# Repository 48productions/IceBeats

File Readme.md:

# IceBeats Music Visualizer
*"it's like a firebeat, but **cooler**"*

## Introduction
IceBeats is a Teensy-based lights driver board that does two things:
 - Works with StepMania to control cabinet and pad lights in a 573-era DDR cabinet.
 - Real-time, hardware independent music visualization across two LED strips.

The hardware is designed for minimal components/configuration for an embedded environment.
Grab a Teensy 3.2, a few addressable LED strips, and a few basic components, and you're done! No bloated bluetooth/wifi control or complex hardware setup required.

## Features
Code support for these are built-in - all 99% configurable, use any combination you like!

 * Visualization addressable LED strip - An addressable RGB LED strip for visualizations.
 * Bass addressable LED strip - Another addressable RGB LED strip, blinks to the beat.
 * Bass single-color LED strip/strand - Designed for a single-color LED strip, or low voltage LED string lights. Blinks to the beat.
     * Supports two-wire LED strands, where alternate LEDs/colors are driven by reversing the strip polarity using a H-Bridge, like the L293D. These are cheap and readibly available off places like Amazon.

 * Accepts audio input via RCA/mono 3.5mm jack (or with modification, any other input the Teensy audio library supports)
 * Designed around Teensy 3.2, other Audio-capable Teensy boards likely compatible (the 4.0 is untested but may work)
 
 * FFT-based music visualization using the Teensy Audio Library
 * Multiple visualization effects and color palettes. Optional dynamic, music-based color palettes available
 * Idle animations for when no music is playing
 
 * Drives 573-era DanceDanceRevolution cabinet/pad lighting (reads SextetStream-formatted data output by StepMania or other programs).
 * PCB design

## Hardware Setup
**Pin numbers and LED strip lengths can ALL be configured in `IceBeats.ino` - the settings are at the top!**

### Audio Input
Audio input is taken via a 3.5mm/RCA jack. [Wiring instructions can be found on the Teensy Audio Design Tool](https://www.pjrc.com/teensy/gui/?info=AudioInputAnalog)'s info panel for AudioInputAnalog.

### Visualization LED strip:
The main attraction, music visualization on an addressable LED strip!

Any WS2812/NeoPixel strip will do here (default: 54 pixels long, but can be configured for shorter/longer strips).
Excessive pixel count may cause performance drops.

### Bass LED strip:
This blinks to the beat with a strip-wide gradient, occasionally changing colors.

Again, use any WS2812/NeoPixel strip (default: 128 pixels. This can be made shorter/longer too)

### Bass light strand:
This one just blinks to the beat! You've got a few options for this:

For a single-color LED strip/string, one PWM pin is used for setting the strip's brightness, just hook it up to a mosfet/transistor and you're good to go.
  
Some cheap LED strings on Amazon will control alternate LEDs, or different LED colors by reversing the strip polarity.
If you have one of these strings, a L293D can be used to drive the strip at two different polarities to turn on alternate LEDs/colors.
Another pin can optionally connect to a L293D to do this. You will need to invert that pin's signal via a transistor, inverter, etc to drive the second input on the L293D.

### StepMania pad/cab light control:
This code accepts input over serial for any games/tools that use the SextetStream protocol for driving DDR cabinet/pad lights.

In the case of StepMania, this means either using the SextetStreamToFile (Linux) or Win32Serial (Windows) lights driver.

The light states are sent to the rest of the Teensy's IO pins. Ideally, these should connect to the DDR cabinet through opto isolators. No transistor/mosfet is needed here, the stock DDR cabinet amp handles the high-current loads.

Lights data can optionally be output to three shift registers, as well, if you need more light outputs than the Teensy has pins.

## Todo:
 There's a lotta things that could be improved
 * Better documentation/wiring instructions
 * A few bugfixes with idle animations on the main led strip
 * Better beat detection
 * Getting the visualizations to look like they reflect the music a bit closer
 * More color palettes.

## License
I'd greatly apprecate it if you credit/link back to this repo if you use this code somewhere - this thing took a TON of time to make.

That being said,

¯\\_(ツ)_/¯

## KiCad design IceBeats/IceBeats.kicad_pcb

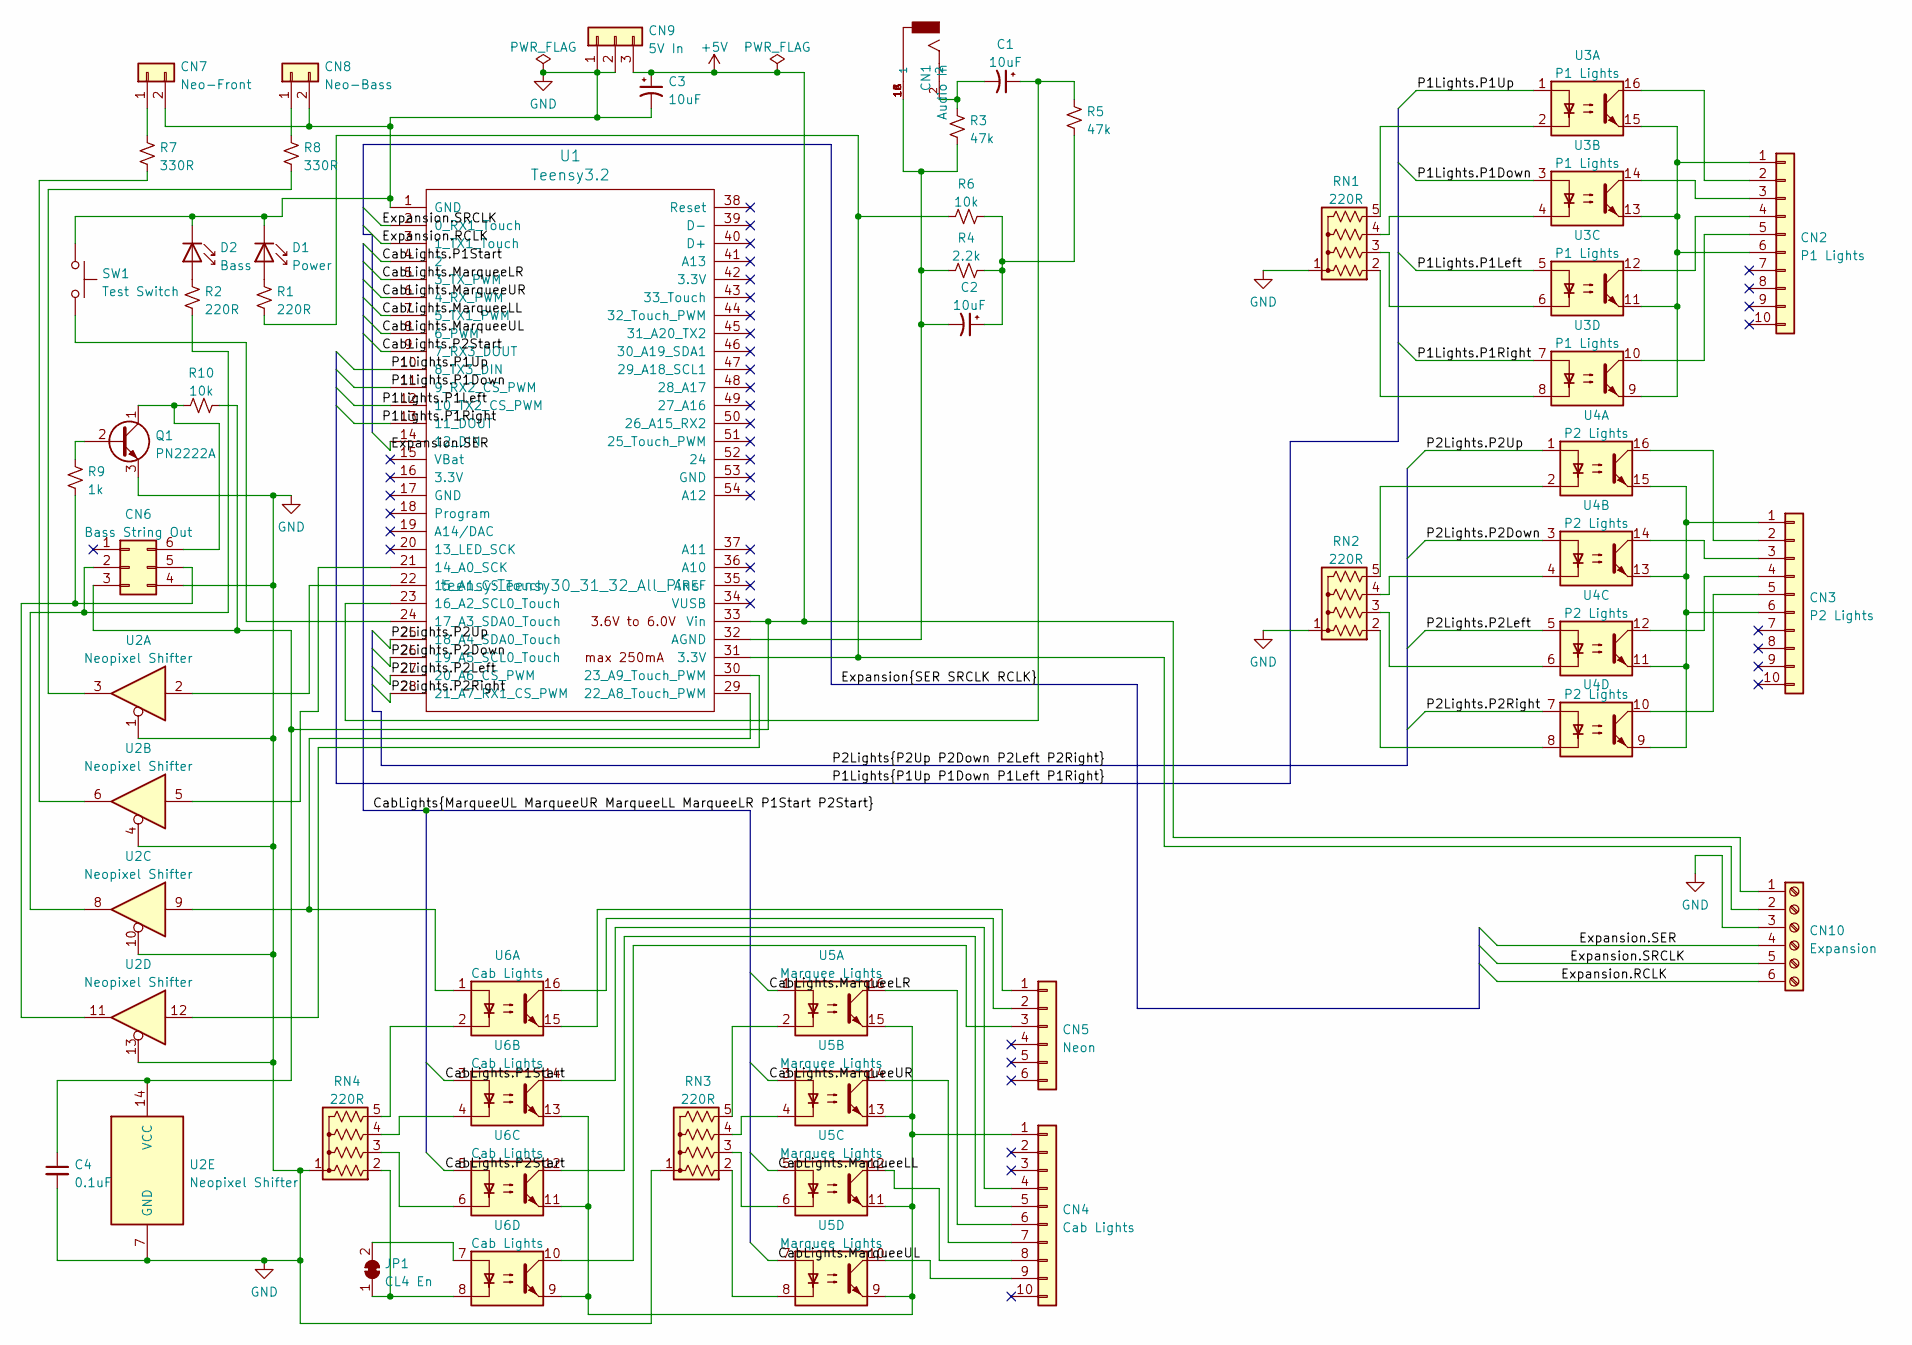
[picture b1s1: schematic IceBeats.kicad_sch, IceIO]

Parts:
C1, C2, C3: 10uF; CP_Radial_D6.3mm_P2.50mm
C4: 0.1uF; C_Disc_D5.1mm_W3.2mm_P5.00mm
CN1: Audio In; CUI_RCJ-013; PART_REV B
CN2: P1 Lights; PinHeader_1x10_P2.54mm_Vertical
CN3: P2 Lights; PinHeader_1x10_P2.54mm_Vertical
CN4: Cab Lights; PinHeader_1x10_P2.54mm_Vertical
CN5: Neon; PinHeader_1x06_P2.54mm_Vertical
CN6: Bass String Out; IDC-Header_2x03_P2.54mm_Vertical
CN7: Neo-Front; Molex_KK-254_AE-6410-02A_1x02_P2.54mm_Vertical
CN8: Neo-Bass; Molex_KK-254_AE-6410-02A_1x02_P2.54mm_Vertical
CN9: 5V In; Molex_KK-254_AE-6410-03A_1x03_P2.54mm_Vertical
CN10: Expansion; PinHeader_1x06_P2.54mm_Vertical
D1: Power; LED_D3.0mm_Horizontal_O3.81mm_Z2.0mm
D2: Bass; LED_D3.0mm_Horizontal_O3.81mm_Z2.0mm
JP1: CL4 En; SolderJumper-2_P1.3mm_Bridged_RoundedPad1.0x1.5mm
Q1: PN2222A; TO-92_HandSolder
R1, R2: 220R; R_Axial_DIN0207_L6.3mm_D2.5mm_P2.54mm_Vertical
R3: 47k; R_Axial_DIN0207_L6.3mm_D2.5mm_P2.54mm_Vertical
R4: 2.2k; R_Axial_DIN0207_L6.3mm_D2.5mm_P10.16mm_Horizontal
R5: 47k; R_Axial_DIN0207_L6.3mm_D2.5mm_P10.16mm_Horizontal
R6, R10: 10k; R_Axial_DIN0207_L6.3mm_D2.5mm_P10.16mm_Horizontal
R7, R8: 330R; R_Axial_DIN0207_L6.3mm_D2.5mm_P10.16mm_Horizontal
R9: 1k; R_Axial_DIN0207_L6.3mm_D2.5mm_P10.16mm_Horizontal
RN1, RN2, RN3, RN4: 220R; R_Array_SIP5
SW1: Test Switch; SW_PUSH_6mm_H5mm
U1: Teensy3.2; Teensy30_31_32_All_Pins
U2: Neopixel Shifter; DIP-14_W7.62mm_Socket
U3: P1 Lights; DIP-16_W7.62mm
U4: P2 Lights; DIP-16_W7.62mm
U5: Marquee Lights; DIP-16_W7.62mm
U6: Cab Lights; DIP-16_W7.62mm

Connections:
+5V: C3.1, C4.1, CN6.3, CN9.3, CN10.1, R10.1, U1.33 (Vin), U2.14 (VCC)
/CabLights.MarqueeLL: U1.7 (5_TX1_PWM), U5.5
/CabLights.MarqueeLR: U1.5 (3_TX_PWM), U5.1
/CabLights.MarqueeUL: U1.8 (6_PWM), U5.7
/CabLights.MarqueeUR: U1.6 (4_RX_PWM), U5.3
/CabLights.P1Start: U1.4 (2), U6.3
/CabLights.P2Start: U1.9 (7_RX3_DOUT), U6.5
/Expansion.RCLK: CN10.6, U1.3 (1_TX1_Touch)
/Expansion.SER: CN10.4, U1.14 (12_DIN)
/Expansion.SRCLK: CN10.5, U1.2 (0_RX1_Touch)
/P1Lights.P1Down: U1.11 (9_RX2_CS_PWM), U3.3
/P1Lights.P1Left: U1.12 (10_TX2_CS_PWM), U3.5
/P1Lights.P1Right: U1.13 (11_DOUT), U3.7
/P1Lights.P1Up: U1.10 (8_TX3_DIN), U3.1
/P2Lights.P2Down: U1.26 (19_A5_SCL0_Touch), U4.3
/P2Lights.P2Left: U1.27 (20_A6_CS_PWM), U4.5
/P2Lights.P2Right: U1.28 (21_A7_RX1_CS_PWM), U4.7
/P2Lights.P2Up: U1.25 (18_A4_SDA0_Touch), U4.1
GND: C3.2, C4.2, CN6.4, CN7.2, CN8.2, CN9.1, CN9.2, CN10.3, D1.1 (K), D2.1 (K), Q1.3 (E), RN1.1 (common), RN2.1 (common), RN3.1 (common), RN4.1 (common), SW1.1, U1.1 (GND), U2.1, U2.4, U2.7 (GND), U2.10, U2.13
unnamed: C1.1, R5.1, U1.23 (16_A2_SCL0_Touch)
unnamed: C1.2, CN1.2, R3.1
unnamed: C2.1, R4.1, R5.2, R6.1
unnamed: C2.2, CN1.1A (1), CN1.1B (1), CN1.1C (1), R3.2, R4.2, U1.32 (AGND)
unnamed: CN2.1, CN2.6, U3.9, U3.11, U3.13, U3.15
unnamed: CN2.2, U3.16
unnamed: CN2.3, U3.14
unnamed: CN2.4, U3.12
unnamed: CN2.5, U3.10
unnamed: CN3.1, CN3.6, U4.9, U4.11, U4.13, U4.15
unnamed: CN3.2, U4.16
unnamed: CN3.3, U4.14
unnamed: CN3.4, U4.12
unnamed: CN3.5, U4.10
unnamed: CN4.1, U5.9, U5.11, U5.13, U5.15, U6.9, U6.11, U6.13
unnamed: CN4.4, U6.14
unnamed: CN4.5, U6.12
unnamed: CN4.6, U5.16
unnamed: CN4.7, U5.14
unnamed: CN4.8, U5.12
unnamed: CN4.9, U5.10
unnamed: CN5.1, U6.15
unnamed: CN5.2, U6.16
unnamed: CN5.3, U6.10
unnamed: CN6.2, R2.2, U2.8
unnamed: CN6.5, R9.2, U2.11
unnamed: CN6.6, Q1.1 (C), R10.2
unnamed: CN7.1, R7.1
unnamed: CN8.1, R8.1
unnamed: CN10.2, R1.2, R6.2, U1.31 (3.3V)
unnamed: D1.2 (A), R1.1
unnamed: D2.2 (A), R2.1
unnamed: JP1.1 (A), RN4.2 (R1), U6.8
unnamed: JP1.2 (B), U6.7
unnamed: Q1.2 (B), R9.1
unnamed: R7.2, U2.6
unnamed: R8.2, U2.3
unnamed: RN1.2 (R1), U3.8
unnamed: RN1.3 (R2), U3.6
unnamed: RN1.4 (R3), U3.4
unnamed: RN1.5 (R4), U3.2
unnamed: RN2.2 (R1), U4.8
unnamed: RN2.3 (R2), U4.6
unnamed: RN2.4 (R3), U4.4
unnamed: RN2.5 (R4), U4.2
unnamed: RN3.2 (R1), U5.8
unnamed: RN3.3 (R2), U5.6
unnamed: RN3.4 (R3), U5.4
unnamed: RN3.5 (R4), U5.2
unnamed: RN4.3 (R2), U6.6
unnamed: RN4.4 (R3), U6.4
unnamed: RN4.5 (R4), U6.2
unnamed: SW1.2, U1.24 (17_A3_SDA0_Touch)
unnamed: U1.21 (14_A0_SCK), U2.5
unnamed: U1.29 (22_A8_Touch_PWM), U2.9, U6.1
unnamed: U1.30 (23_A9_Touch_PWM), U2.12
unnamed: U1.22 (15_A1_CS_Touch), U2.2

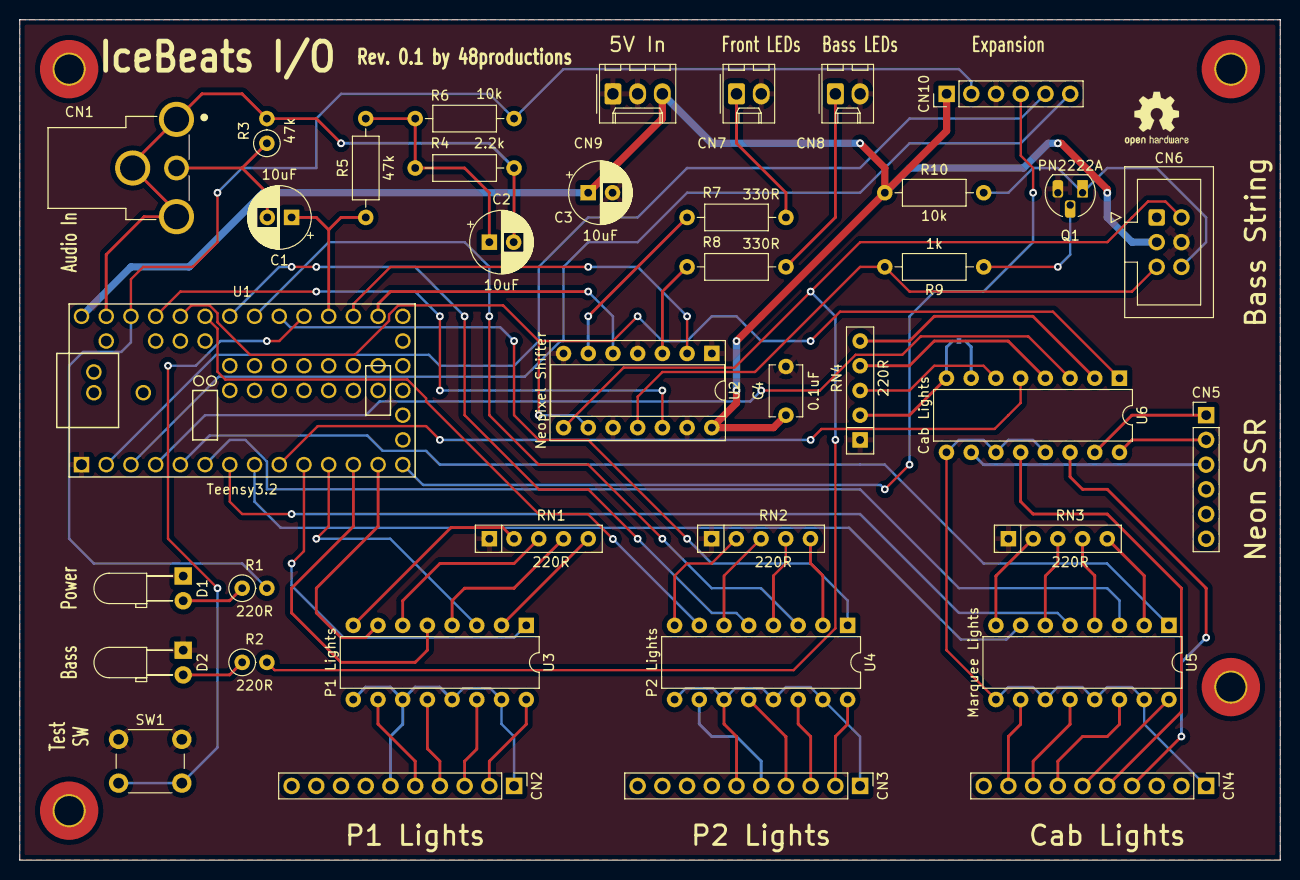
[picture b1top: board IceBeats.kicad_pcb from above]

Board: 2 copper layers, 129.5 x 86.4 mm, 39 parts (1 on the bottom side), 76 nets.

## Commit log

2020-07-25 Effect Kick no longer sucks, other effect improvements
    Lots of changes to make visualization effects not be trash!
    - Kick now always draws non-bass sections across the entire strip, and fits more non-bass sections on the strip
    - Kick's bass section is now overlaid on top of whatever the rest of the strip is doing
    - Pulse and Punch now pulse the strip's brightness to the beat
    - Bass kicks are visualized on the built-in LED on the Teensy
    - TODO: Beat detection is still buggy as frick
2020-07-27 Beat detection is slightly less drunk (but still not perfect)
    Trying to detect peaks from the bass section of the FFT to detect bass kicks, needs some tweaking 100% but looks promising.
2020-07-30 IceBeats: Now with AGC and better beat detection!
    * Songs should visualize similarly regardless of the input's volume - hyper quiet songs no longer only turn on 1 LED, hyper loud songs no longer always max out all the LEDs
    * The threshold to detect a beat at now decreases if beats aren't seen for a bit
2020-08-04 Cabinet button input, improved other stuff
    - Inputs on some specific pins (tentative, likely to change) now send keystrokes
    - /shrug, everything else seems better now too
2020-08-11 "Driving input with my lights driver is probably a dumb idea"
    Also made idle animations functional and implemented an idle animation :ok_hand:
2020-08-12 Alternating bass kick lights, better light state transitions
    - Have a light string that you can drive in two polarities with an H-bridge that you want to use as bass lights? That's oddly specific but it's here now anyways.
    - Bass lights transition between visualizations/idle animations/nothing better
    - Slightly more lenient beat detection
    - Beat detection is still trash tho
2020-08-14 SIGNIFICANTLY improved beat detection
    - Pros: New bass kick detection method, based on tracking how much the bass changes each FFT read and how far above this average the current bass change is
    - Cons: No longer works on Brain Power
    - Pros: Works at least decently well on most of the songs I've tried so far
    - Cons: No really this method doesn't work on Brain Power please don't try it :(
2020-08-18 Add light test, tweak beat detection
    - Added light test mode - Blinks all lights and cycles colors on the LED strip
    - Beat detection handles quieter songs better
    - Bass kick length is now dynamic and based on the music (with an upper limit) instead of being hard coded to 125ms
    - Fixed some beat-based effects in VEPulse/VEPunch
    - Section brightness in VE Kick now depends on how loud that section is
2020-08-28 Volume control, cabinet lighting
    Also pin reassignments lol, cab lighting currently untested
2020-09-01 Better AGC, maybe better beat detection?
    - Added Visualization Effect: Volume
    - Gently coax AGC to actually work (compensation for low cab/song volume - Great if your speakers are turned down to 1 but you still want LED brightness turned up to 11)
    - Implemented detection for the current non-bass FFT level - If this level is lower than average, bass kick detection is made slightly more lenient (Though not by much yet, thanks to Yumry for the su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
2020-09-05 Partial new Visualization Effect implementation
2020-09-10 Marquee lighting garbo
    - Rearrange pins again
    - Marquee lights are now on dedicated MCU pins (and now smoothly fade on/off)
    - Bass and select lights are now mapped to the shift register cab lights used to be on
2020-09-16 tfw you break your board design
2020-09-17 Add burn-in, unfinished exp. filtering
2020-09-18 No burnin plz
2020-09-18 My code is not ready
    - Reversed volume up/down pins
    - *Hopefully* disabled fancy marquee lighting (my cab said no, away it goes)
2020-10-07 VE Pitch actually kinda works now
    Todo: Bass is overemphasized, mids should be emphasized more
2020-10-18 Experimental palette swapping - Very buggy
    Disable more fancy cab light stuff
2020-10-30 Make VE Pitch look nicer
    ...but not perfect.
    Also tweak the "big change in music" detection to not be ultra spazzy.
2020-11-04 Frequency -> Color = Maybe??? (WIP, broken)
    - Pitch LED offset tidy
    - A generic-ish "frequency to color" conversion is done. In the future this might help decide color palettes. For now, it's mapped to pixel #0.
    TODO: Less temporary hardcoded jank, more actually working code (like always)
2020-11-05 Big Code Tidy MK.1
    Refactor our HUGE single ino file to use separate files for cleanliness points.
    Rest in peace almost 1300 line long IceBeats.ino, long live proper organization!
2020-11-09 Frequency -> Color? (Suggested by Yumry), BIG tidy
    - The strip palette is now based on a common frequency -> color conversion (experimental, thanks Yumry for the suggestion!)
    - Big code tidy the second: Main loop update functions are in their own ino file now, let's break git because why not lol.
    - Stop writing outside of arrays in the common frequency detection (Fixes glitchiness in VE Kick, I WARNED you about the ARRAYS, DOG!)
2020-11-16 Big Tidy MK.3: Faster, less ghetto visualization update rate
    Big Tidy MK.3: The main loop's update rate was dependent on both a delay() call and how fast the FFT could update - pretty jank.
    Now we're 100% dependent on keeping a solid 60fps, which I'm assuming will translate to improvements elsewhere (like the update-rate dependent beat detection). :ok_hand:
    Some fun facts about how fast updates happen:
    - Before: Every 20-24ish ms (40-50fps)
    - No delays: 10-15ms (66-100fps)
    - Current: Fairly smooth 16ms (60fps)
2020-11-17 Partial bass LED strip support
    I tried before and failed. Now that things are a tad less buggy, let's goooo!
    (Todo: Stepmania control)
    Also: Rewrite readme, tweak beat detection since we're running at a different update rate now
2020-11-24 Auto visualization swapping, AGC tweak
2020-11-24 Brightness/AGC tweaks again
2020-12-02 SM-Controlled Bass Neon LED Strip
    - The bass neon LED strips automagically switch between SM and audio reactive control
    - Cleanup of bass led strip code
2020-12-02 Basically bases bass kicks off SM's bass neon output
2020-12-17 Make music-based palettes an option
    - Choosing between music-based and pre-set color palettes is now an option
    - Pre-set color palettes now auto-swap
    - Disabled more fadeable marquee light garbage
2021-01-04 Alternative SM-based VE (to be removed)
    An experimental, half-broken rewrite of VE Pulse to blink four strip sections to SM's marquee lighting output, also brings back marquee light fading (internally) and adds smoother fades on/off to it.
    It's not a *terrible* effect in-game, but it's not great in menus and wouldn't look good if it was reading marquee lighting from non-stepmania games (say, if I read lighting output from a 573 - real 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
    Away it goes eventually, but committing so that it's at least saved somewhere before being nuked into oblivion.
2021-01-11 Memory tweaks, bass LED strip tweak
    - Reduce memory allocation for the audio library (only really used like half the memory I allocated for it, it seems)
    - Flip the direction the bass LED strip draws in
    - Disable keyboard support
    There's some leftover code from trying to troubleshoot an issue where too many LEDs on the bass LED strip completely borks several millis-related things. *Not* using oodles of pixels is a hard sell, 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
2021-01-11 Release finalization
    - Disable some debugging stuff
    - Disable VE Pulse
2021-01-14 MMMMMMMMMMMMMMMMMMMMMMMMMMM
    The data array for the bass LED strip is now initialized properly
    This fixes a bug where if the bass LED strip was made longer than the main one, random values would get written into millis and completely NUKE a heckton of other functionality.
2021-01-14 Light test, bass kick scroll improvements
    - Light test now tests both strips, and has a rainbow test
    - Two positions/colors for bass kick scrolling LEDs are now tracked
2021-01-20 Readme tweak, meme output
2021-02-07 New bass LED strip VE, cleanup
    - Tried to make a new VE again (haha nope)
    - Cleaned bass kick LED scrolling code a tad
    - Bass LED strip effects that alter the hue across the strip now scale with strip size
    - Bass kicks on the bass LED strip can be visualized in two slightly different ways now
2021-02-10 Fade between palette changes
    - Palette changes now briefly fade between the old and new palettes
    - Random palette swaps will no longer swap from one palette to the exact same palette
2021-02-20 Experimental: Waver the current palette's hue to the beat
    - In preset palette mode, the palette in use is now wavered a tad (vaguely) to the beat to add some more flavor to visualizations. This is mostly proof of concept, probably gonna get polished some mo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
    - The last bass kick timestamp is now reset when exiting idle (throws off bass kick length calculation for a bit otherwise)
2021-02-24 Bass strip polishing
    - Default to 144-long bass strips again
    - Strip hue waver is now configurable
    - The position on the bass strip that effects start at (edges or center) is now also configurable
    - Bass strip hue shift config tweaked, now allows for more granularity (hue shift went from short to float)
2021-02-24 Fix bass hue offset bug
2021-02-25 Release tweaks
2021-02-28 Fix most serial lighting outputs being broken
    Meme output commit was too way memey. Your guess as to why it broke is as good as mine, but apparently Arduino *really* didn't want to bitRead directly into variables.
2021-03-01 New idle animation
    - The existing idle animation looks slightly less like unicorn barf
    - A new idle animation exists!
2021-06-11 More pinout changes
    This week on "48 rewires his DDR cab for the 50th time": Marquee/button lighting has a new pinout for questionable reasons!
2021-08-25 Tweaks for the final installation
2021-08-30 "Even FEWER Blinking Lights?!"
2021-12-07 MMMMMM
2022-10-29 Add IceBeats I/O PCB
    NEW! PCB design for those interested in an I/O solution better than just parts on a perfboard!
    - Add KiCad schematics for I/O PCB
    - Modify firmware to accompany I/O PCB - light outputs no longer require shift registers
    - Accompanying documentation update
2023-01-31 Fix lighting pinouts (not jank edition)
2023-03-19 Rework Bass String H-Bridge for Adafruit DRV8871
